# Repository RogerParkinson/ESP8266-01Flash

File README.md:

# ESP8266-01Flash
Breadboard friendly breakout for an ESP8266-01.
The Eagle files for a board to allow you to conventiently flash an ESP8266-01 from Arduino IDE.
It is also shared at [OSHPark](https://oshpark.com/shared_projects/DmLE6lQu)
See my [blog post](https://madurasoftware.com/blog/esp8266-01-flashing-tool) for more details.

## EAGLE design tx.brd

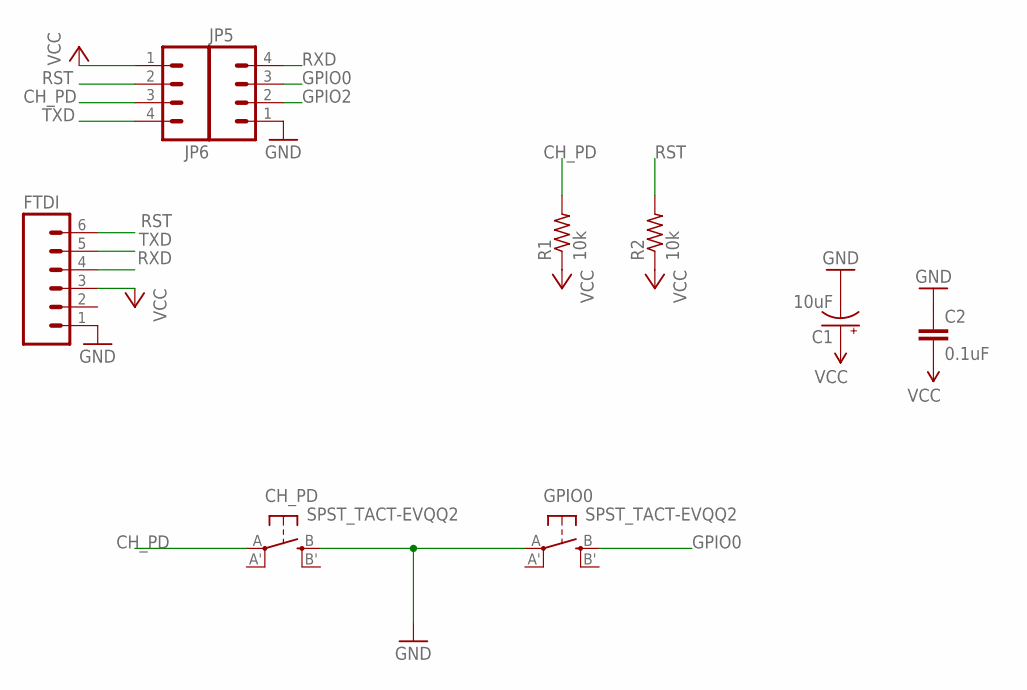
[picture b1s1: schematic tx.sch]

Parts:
C1: 10uF; EIA6032
C2: 0.1uF; 0603-CAP
CH_PD: SPST_TACT-EVQQ2; EVQ-Q2
FTDI: M06SILK_FEMALE_PTH; 1X06
GPIO0: SPST_TACT-EVQQ2; EVQ-Q2
JP5, JP6: M041X04_NO_SILK; 1X04_NO_SILK
R1, R2: 10k; R0805

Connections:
CH_PD: CH_PD.A, JP6.3, R1.2
GND: C1.P$2 (-), C2.1, CH_PD.B (S), FTDI.1, GPIO0.A, JP5.1
GPIO0: GPIO0.B (S), JP5.3
GPIO2: JP5.2
RST: FTDI.6, JP6.2, R2.2
RXD: FTDI.4, JP5.4
TXD: FTDI.5, JP6.4
VCC: C1.P$1 (+), C2.2, FTDI.3, JP6.1, R1.1, R2.1

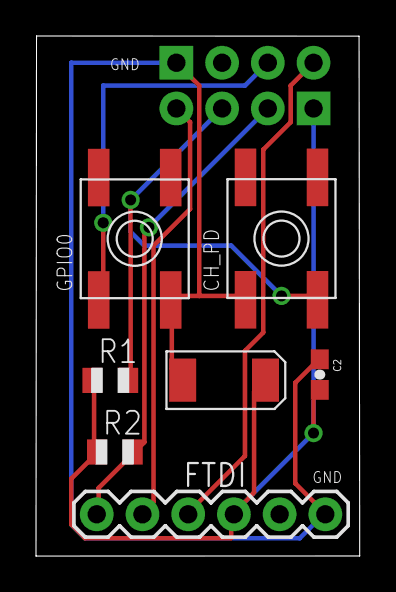
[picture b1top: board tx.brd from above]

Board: 2 copper layers, 18.0 x 28.9 mm, 9 parts (0 on the bottom side), 7 nets.

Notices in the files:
tx.brd:
(c) 2017 Roger Parkinson
parts and their libraries:
SparkFun-Connectors: Licensing: Creative Commons ShareAlike 4.0 International - https://creativecommons.org/licenses/by-sa/4.0
